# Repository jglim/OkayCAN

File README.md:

# OkayCAN

*The okayest ESP32-S2 CAN development board*

## Features

- Essentially an ESP32-S2 with a CAN transceiver and supporting components.
- Native USB support, saving on an additional USB-UART chip.
- Designed to fit a commonly available OBD enclosure and its 16-pin connectors.
- Each board should cost about US$10 each when assembling about 10 boards, making it fairly affordable in small runs.
- Easy to assemble/manufacture, as all components are on a single side, and most components are surface mounted.
- Uses a USB-C connector, which is easier to interface when the device is installed in difficult-to-reach places.

### Free

This project is permissively licensed (MIT)

- No restrictions and no royalties on private / commercial use.
- The design files (schematic, board) can be downloaded and modified to fit your own requirements.
- Ready-to-use manufacturing files (gerbers, BOM) are also available. Send it to your preferred fab to have the boards made.
- Please feel free to sell the boards that you have made, even if it is a 1:1 clone. There is no need for attribution too.
- The selected [iso-tp stack](https://github.com/lishen2/isotp-c) from [lishen2](https://github.com/lishen2/) that is included in the examples is also MIT-licensed.

---

## Get an OkayCAN

**Build it yourself**

- PCB: [Gerbers are zipped](https://github.com/jglim/OkayCAN/raw/main/Hardware/V1.1/OkayCAN/gerbers/OkayCAN_fab_gerbers_211101.zip) and ready to be uploaded to your fab
- BOM: Almost every component has a matching LCSC part number, and [the CSV](https://github.com/jglim/OkayCAN/blob/main/Hardware/V1.0/OkayCAN/raster/OkayCAN_BOM.csv) works with their BOM upload feature.
    - The only odd part is the OBD2 header (with case), which has to be sourced from marketplaces like Aliexpress
- Assembly: as most of the parts are surface-mounted, getting a stencil will make the process much quicker.

**Buy one**

I'm not assembling any for sale at this time, though I would love to see it being accessible to more people. If you decide to sell complete boards, please let me know so that I may be able to share about it. Everyone is welcome to create and sell clones/variants of the OkayCAN.

---

## Firmware

**[OkayCAN_GettingStarted](https://github.com/jglim/OkayCAN/tree/main/Firmware/Examples/OkayCAN_GettingStarted)**

Get started quickly with this example, which queries a (MB) ECU for parameters such as VIN, part number, and software versions, then displays it on the serial port.

The example will demonstrate communications with an ECU over UDS (a layer above CAN), as well as usage of the serial port over USB CDC. When working properly, the serial should show an output similar to this:

```
Voltage: 11993 mV
00000BBE TX ISO-TP: 22 F1 8C
00000BC3 RX ISO-TP: 62 F1 8C 33 31 33 31 XX XX XX XX
Received Serial Number: 3131XXXX
Voltage: 11979 mV
00000FA7 TX ISO-TP: 22 F1 90
00000FAC RX ISO-TP: 62 F1 90 57 44 44 32 34 36 32 30 30 31 4A XX XX XX XX XX XX
Received VIN Original: WDD2462001JXXXXXX
Voltage: 12003 mV
00001390 TX ISO-TP: 22 F1 A0
00001394 RX ISO-TP: 62 F1 A0 57 44 44 32 34 36 32 30 30 31 4A XX XX XX XX XX XX
Received VIN Current: WDD2462001JXXXXXX
Voltage: 12003 mV
00001779 TX ISO-TP: 22 F1 21
00001783 RX ISO-TP: 62 F1 21 36 35 31 39 30 34 30 33 30 31 36 35 31 39 30 32 33 31 30 31 36 35 31 39 30 33 31 34 33 31
Received Software block data:
6519040301
6519023101
6519031431
Voltage: 11984 mV
00001B62 TX ISO-TP: 22 F1 00
00001B67 RX ISO-TP: 62 F1 00 02 21 31 01
Received Variant ID: 2131
Voltage: 12003 mV
00001F4B TX ISO-TP: 22 F1 11
00001F50 RX ISO-TP: 62 F1 11 36 35 31 39 30 31 30 36 30 31
Received Part Number: 6519010601
...
```

**[OkayCAN_OBD](https://github.com/jglim/OkayCAN/tree/main/Firmware/Examples/OkayCAN_OBD)**

_UNVERIFIED: No vehicle to test on; tested against a simulated ecu on another esp32. Please let me know if this works! --jg_

Queries an OBD-II compliant ECU for its engine speed, vehicle speed, and throttle position. These parameters are typically supported by most ECUs.

A open Wi-Fi network with the name "OkayCAN-OBD" is also created, and serves a simple web page over http at [192.168.4.1](http://192.168.4.1/) . The page shows real-time results of the OBD queries as JSON if they are available.

---

## Hardware

⚠️ Warning: components are rated for 12V only! Please do not connect to 24V systems.

### OkayCAN V1.0

*Please use the newer V1.1 as it addresses a board outline issue*

**Schematic [(PDF)](https://github.com/jglim/OkayCAN/blob/main/Hardware/V1.0/OkayCAN/raster/OkayCAN_Schematic.pdf)**

TL;DR:
**Power**: Vin (USB: 5V, OBD: 12V) with a diode "OR" into a 3.3V buck regulator (MT1470).
**uC**: CAN_TX @ GPIO5, CAN_RX @ GPIO4, VSENSE @ GPIO2 (Divider ratio: Vin-10K,1.6K-GND)
**OBD**: Only CAN TX/RX, VBATT and *chassis* GND are connected. Other pins are NC.

⚠️ The MT1470 regulator only starts operating at 4.5V, which leaves a small margin for the schottky's forward voltage when running off 5V from USB.

ℹ️ The optional 120R CAN resistors should **not** be populated for normal operation as the bus on the vehicle's port normally includes termination resistors.

ℹ️ Test points are available on the back. The ESP32-S2 can also be flashed with an external USB-UART with these test points (like the regular ESP32).

**Board**

ℹ️ V1.0 requires a minor case modification to fit properly, as the OBD connector's sides are too wide. There are two small plastic tabs on the case, near the OBD header which can be safely removed to allow the board to fit properly.

**BOM**

Available [here](https://github.com/jglim/OkayCAN/blob/main/Hardware/V1.0/OkayCAN/raster/OkayCAN_BOM.csv). Budgetary component prices available in [this extended BOM](https://github.com/jglim/OkayCAN/blob/main/Hardware/V1.0/OkayCAN/raster/OkayCAN_Price_Breakdown.csv).

---

### OkayCAN V1.1

*Latest version*

Minor revision to V1.0

- Adjusted board outline to fit the standard cases without modifications
- Added an optional user LED to GPIO16, unpopulated by default
- Minor routing improvements, footprint positions are unchanged and a stencil from V1.0 will still work on this board

---

## DFU

The ESP32-S2 has a USB ROM bootloader which is read-only. This guarantees that a faulty firmware will not brick the device.
OkayCAN includes BOOT and RESET buttons which can be used to bring the device into DFU, to upload a new firmware.

*Enter DFU mode with these steps:*

1. Press BOOT button
2. Press RESET button
3. Release RESET button
4. Release BOOT button

The device can also be put into DFU mode using only the BOOT button. Hold down BOOT while disconnecting and reconnecting the USB cable, then release BOOT.

After flashing the firmware, remember to press RESET once, or reconnect the USB cable to exit DFU and start running your firmware.

---

## Contributing

Please..

- Build cool stuff with the OkayCAN (and let me know if you do, too!).
- Point out and suggest fixes if there are any issues with the hardware design or firmware.
- Add or improve on the existing examples.
- If you fab these boards with a pick-and-place, I would love to hear about your experience.

Need ideas on what to build? Here are some ideas:

- Control an instrument cluster for your racing or truck sim.
- A vehicle communications interface e.g. a J2534 interface.
- Wireless coding/tuning/upgrading via your phone
- Race telemetry/logger with digital gauges

---

## License

MIT

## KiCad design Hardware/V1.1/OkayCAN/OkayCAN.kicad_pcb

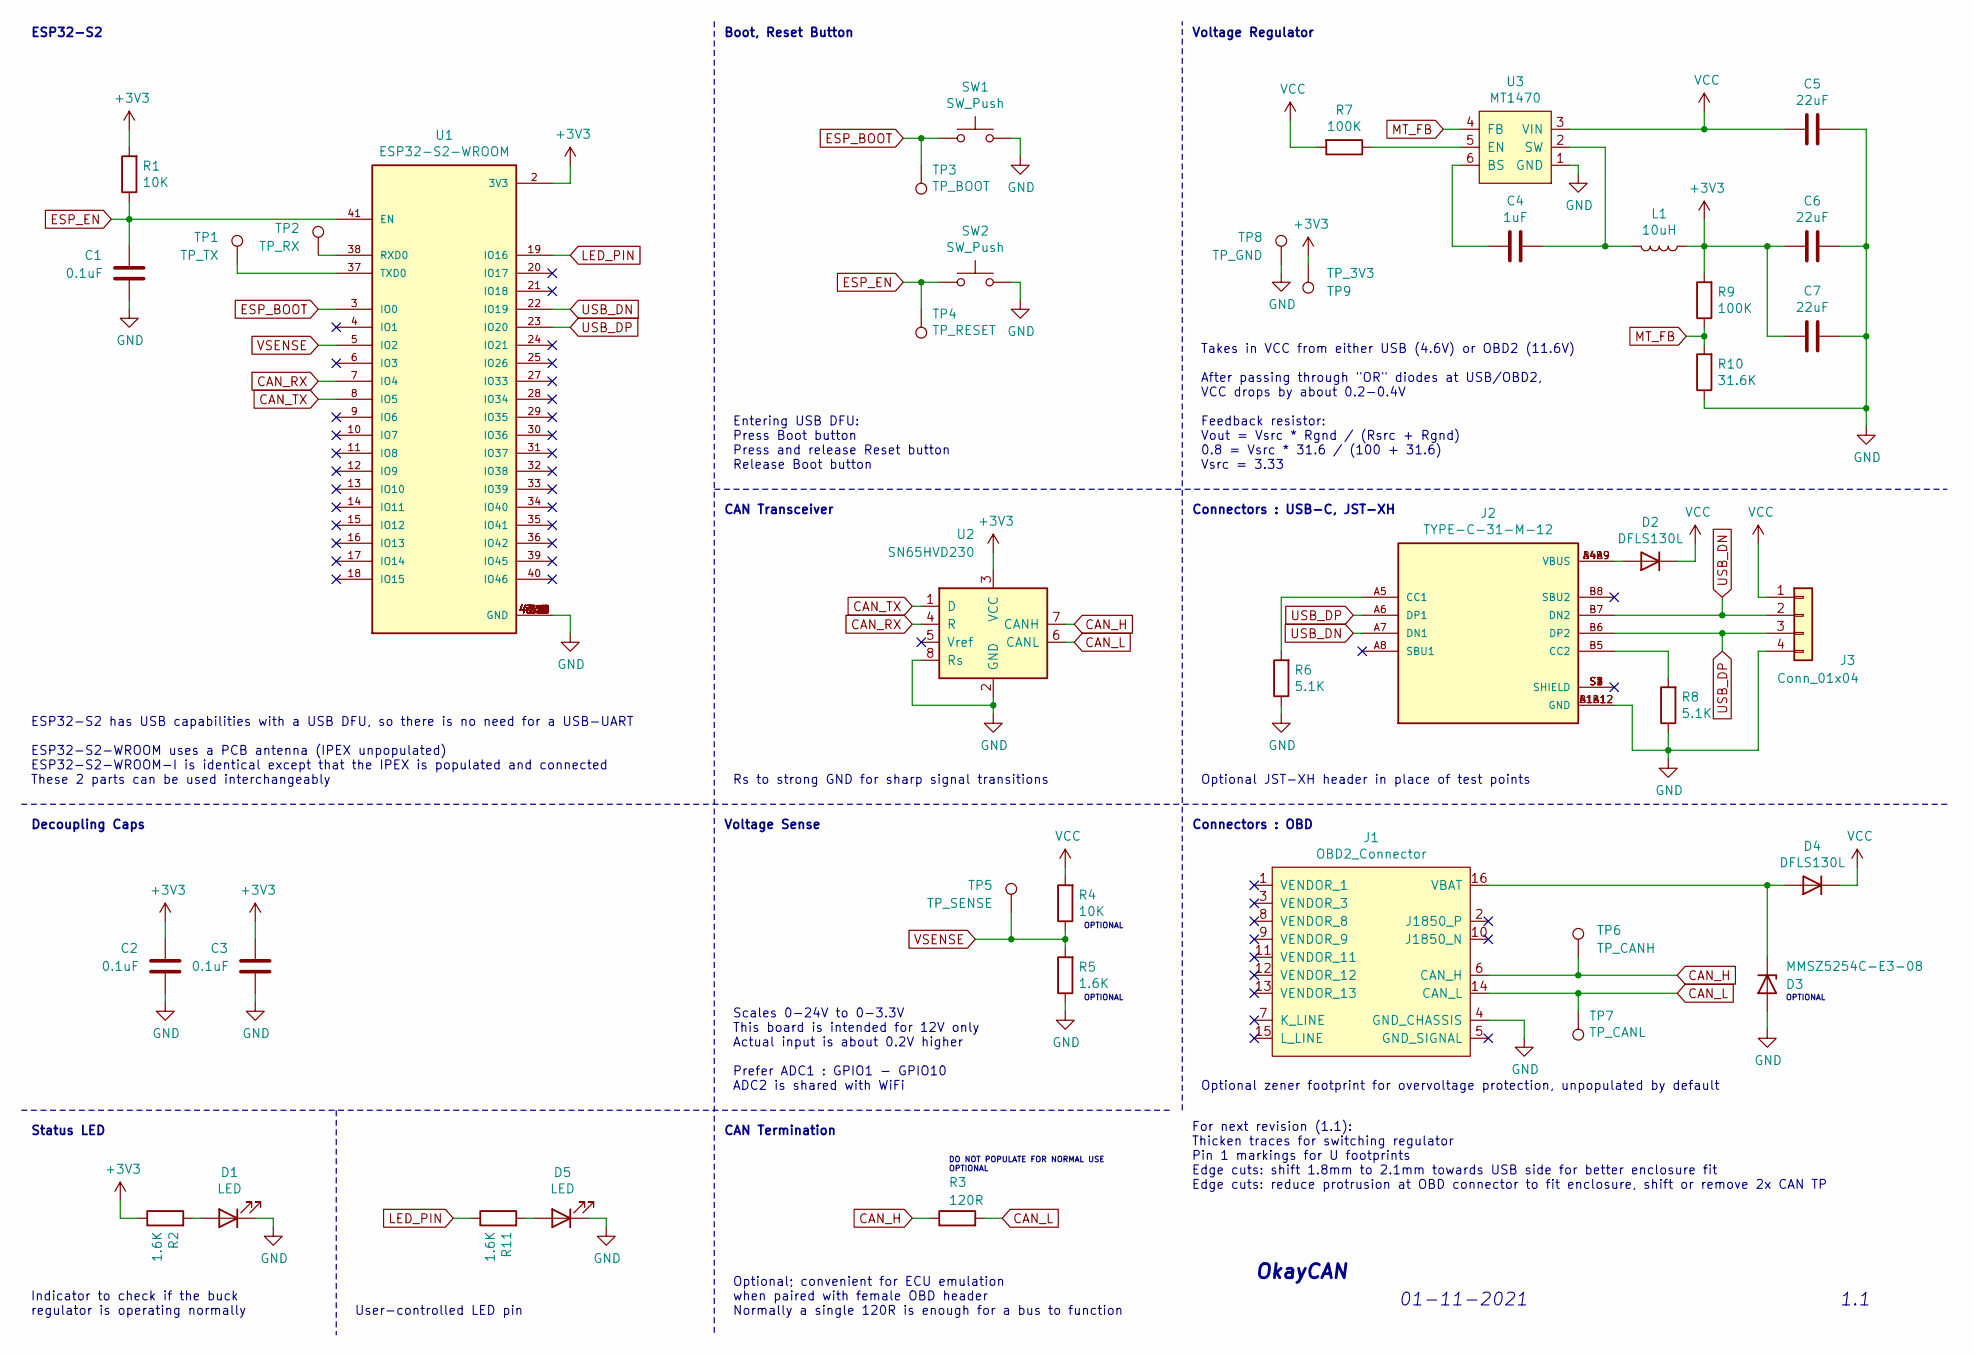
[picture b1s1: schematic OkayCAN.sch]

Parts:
C1, C2, C3: 0.1uF; C_0805_2012Metric_Pad1.15x1.40mm_HandSolder; LCSC C138340
C4: 1uF; C_0805_2012Metric_Pad1.15x1.40mm_HandSolder; LCSC C28323
C5, C6, C7: 22uF; C_0805_2012Metric_Pad1.15x1.40mm_HandSolder; LCSC C45783
D1, D5: LED; LED_0805_2012Metric_Pad1.15x1.40mm_HandSolder; LCSC C84259
D2, D4: DFLS130L; D_PowerDI-123; LCSC C110493
D3: MMSZ5254C-E3-08; D_SOD-123; LCSC C241953
J1: OBD2_Connector; OBD-Male
J2: TYPE-C-31-M-12; HRO_TYPE-C-31-M-12; PARTREV A; LCSC C165948
J3: Conn_01x04; JST_XH_B4B-XH-AM_1x04_P2.50mm_Vertical; LCSC C161871
L1: 10uH; CHILSIN-LVF303012; LCSC C142153
R1, R4: 10K; R_0805_2012Metric_Pad1.15x1.40mm_HandSolder; LCSC C84376
R2, R5, R11: 1.6K; R_0805_2012Metric_Pad1.15x1.40mm_HandSolder; LCSC C17394
R3: 120R; R_1206_3216Metric_Pad1.42x1.75mm_HandSolder; LCSC C175512
R6, R8: 5.1K; R_0805_2012Metric_Pad1.15x1.40mm_HandSolder; LCSC C336831
R7, R9: 100K; R_0805_2012Metric_Pad1.15x1.40mm_HandSolder; LCSC C96346
R10: 31.6K; R_0805_2012Metric_Pad1.15x1.40mm_HandSolder; LCSC C228743
SW1, SW2: SW_Push; HRO-K2-1807; LCSC C502307
TP1: TP_TX; TestPoint_Pad_D1.0mm
TP2: TP_RX; TestPoint_Pad_D1.0mm
TP3: TP_BOOT; TestPoint_Pad_D1.0mm
TP4: TP_RESET; TestPoint_Pad_D1.0mm
TP5: TP_SENSE; TestPoint_Pad_D1.0mm
TP6: TP_CANH; TestPoint_Pad_D1.0mm
TP7: TP_CANL; TestPoint_Pad_D1.0mm
TP8: TP_GND; TestPoint_Pad_D1.0mm
TP9: TP_3V3; TestPoint_Pad_D1.0mm
U1: ESP32-S2-WROOM; XCVR_ESP32-S2-WROOM; PARTREV V1.0; LCSC C967025
U2: SN65HVD230; SOIC-8_3.9x4.9mm_P1.27mm; LCSC C12084
U3: MT1470; SOT-23-6_Handsoldering; LCSC C181781

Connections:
+3V3: C2.1, C3.1, C6.2, C7.2, L1.1, R1.2, R2.1, R9.2, TP9.1, U1.2 (3V3), U2.3 (VCC)
CAN_H: J1.6 (CAN_H), R3.1, TP6.1, U2.7 (CANH)
CAN_L: J1.14 (CAN_L), R3.2, TP7.1, U2.6 (CANL)
CAN_RX: U1.7 (IO4), U2.4 (R)
CAN_TX: U1.8 (IO5), U2.1 (D)
ESP_BOOT: SW1.1, TP3.1, U1.3 (IO0)
ESP_EN: C1.1, R1.1, SW2.1, TP4.1, U1.41 (EN)
GND: C1.2, C2.2, C3.2, C5.1, C6.1, C7.1, D1.1 (K), D3.2 (A), D5.1 (K), J1.4 (GND_CHASSIS), J2.A1B12 (GND), J2.B1A12 (GND), J3.4, R5.1, R6.1, R8.1, R10.1, SW1.2, SW2.2, TP8.1, U1.1 (GND), U1.26 (GND), U1.42 (GND), U1.43.1 (GND), U1.43.2 (GND), U1.43.3 (GND), U1.43.4 (GND), U1.43.5 (GND), U1.43.6 (GND), U1.43.7 (GND), U1.43.8 (GND), U1.43.9 (GND), U1.43.10 (GND), U1.43.11 (GND), U1.43.12 (GND), U1.43.13 (GND), U1.43.14 (GND), U1.43.15 (GND), U1.43.16 (GND), U1.43.17 (GND), U1.43.18 (GND), U1.43.19 (GND), U1.43.20 (GND), U1.43.21 (GND), U2.2 (GND), U2.8 (Rs), U3.1 (GND)
LED_PIN: R11.1, U1.19 (IO16)
MT_FB: R9.1, R10.2, U3.4 (FB)
unnamed: C4.1, L1.2, U3.2 (SW)
unnamed: C4.2, U3.6 (BS)
unnamed: D1.2 (A), R2.2
unnamed: D2.2 (A), J2.A4B9 (VBUS), J2.B4A9 (VBUS)
unnamed: D3.1 (K), D4.2 (A), J1.16 (VBAT)
unnamed: D5.2 (A), R11.2
unnamed: J2.A5 (CC1), R6.2
unnamed: J2.B5 (CC2), R8.2
unnamed: J2.S1 (SHIELD), J2.S2 (SHIELD), J2.S3 (SHIELD), J2.S4 (SHIELD)
unnamed: R7.1, U3.5 (EN)
unnamed: TP1.1, U1.37 (TXD0)
unnamed: TP2.1, U1.38 (RXD0)
USB_DN: J2.A7 (DN1), J2.B7 (DN2), J3.2, U1.22 (IO19)
USB_DP: J2.A6 (DP1), J2.B6 (DP2), J3.3, U1.23 (IO20)
VCC: C5.2, D2.1 (K), D4.1 (K), J3.1, R4.2, R7.2, U3.3 (VIN)
VSENSE: R4.1, R5.2, TP5.1, U1.5 (IO2)

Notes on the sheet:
Takes in VCC from either USB (4.6V) or OBD2 (11.6V) After passing through "OR" diodes at USB/OBD2, VCC drops by about 0.2-0.4V Feedback resistor: Vout = Vsrc * Rgnd / (Rsrc + Rgnd) 0.8 = Vsrc * 31.6 / (100 + 31.6) Vsrc = 3.33
Voltage Regulator
Connectors : USB-C, JST-XH
ESP32-S2
Boot, Reset Button
Voltage Sense
Scales 0-24V to 0-3.3V This board is intended for 12V only Actual input is about 0.2V higher Prefer ADC1 : GPIO1 - GPIO10 ADC2 is shared with WiFi
CAN Transceiver
Optional zener footprint for overvoltage protection, unpopulated by default
Optional JST-XH header in place of test points
Connectors : OBD
Decoupling Caps
Rs to strong GND for sharp signal transitions
Entering USB DFU: Press Boot button Press and release Reset button Release Boot button
CAN Termination
Optional; convenient for ECU emulation when paired with female OBD header Normally a single 120R is enough for a bus to function
OPTIONAL
Status LED
Indicator to check if the buck regulator is operating normally
ESP32-S2 has USB capabilities with a USB DFU, so there is no need for a USB-UART ESP32-S2-WROOM uses a PCB antenna (IPEX unpopulated) ESP32-S2-WROOM-I is identical except that the IPEX is populated and connected These 2 parts can be used interchangeably
For next revision (1.1): Thicken traces for switching regulator Pin 1 markings for U footprints Edge cuts: shift 1.8mm to 2.1mm towards USB side for better enclosure fit Edge cuts: reduce protrusion at OBD connector to fit enclosure, shift or remove 2x CAN TP
DO NOT POPULATE FOR NORMAL USE
OkayCAN
1.1
01-11-2021
User-controlled LED pin

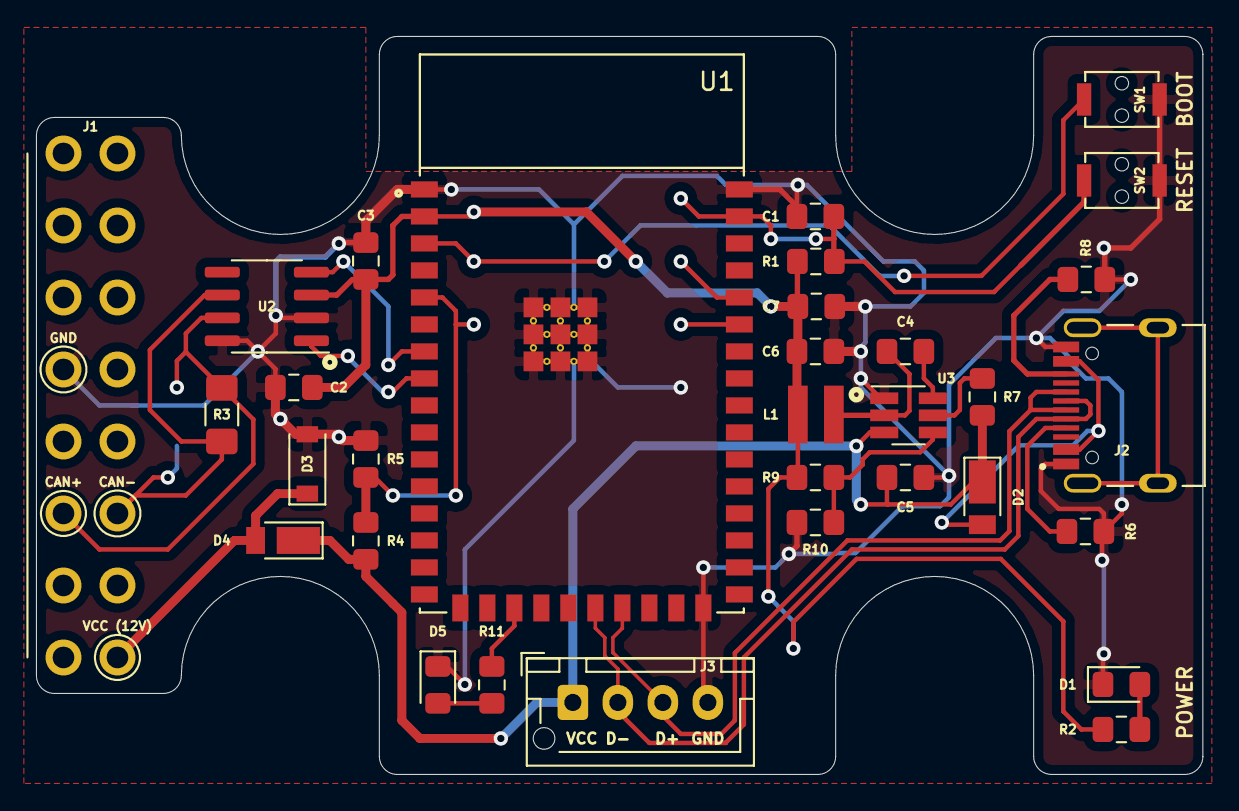
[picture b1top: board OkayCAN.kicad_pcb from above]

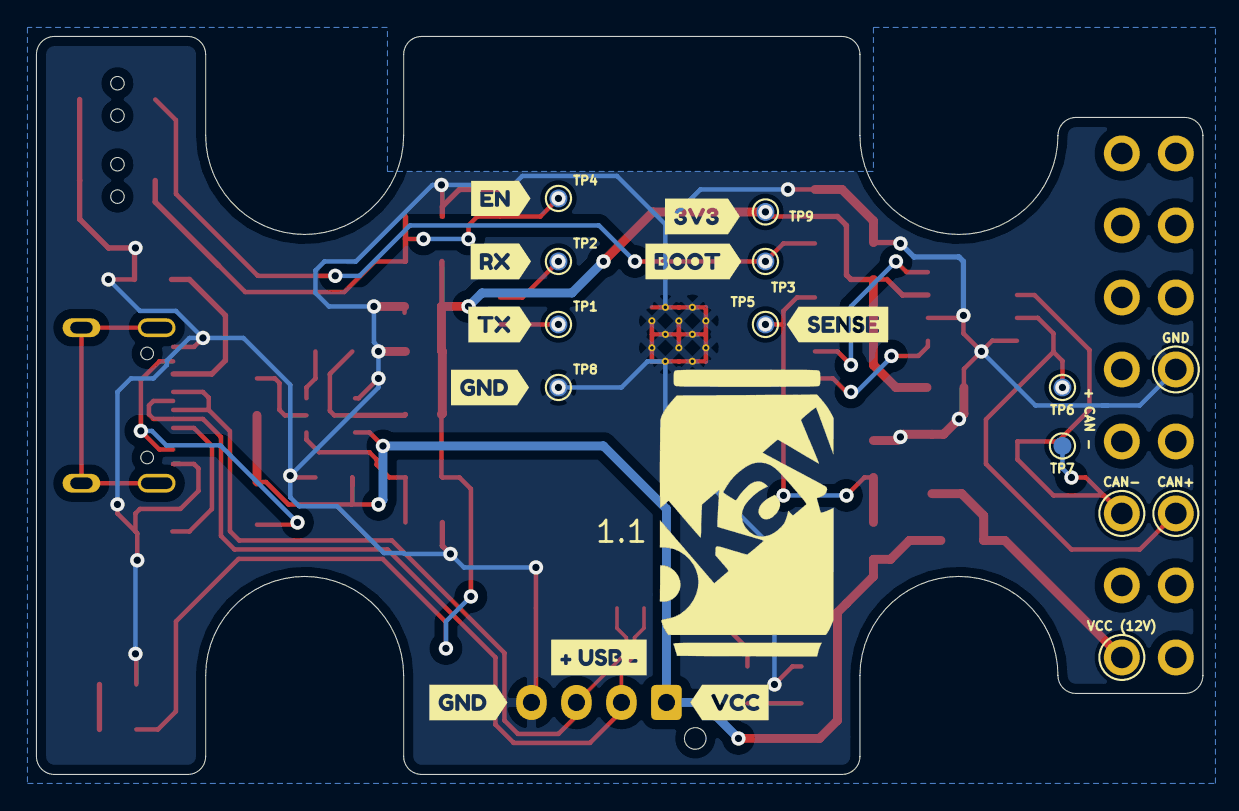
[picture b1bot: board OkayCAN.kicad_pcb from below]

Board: 2 copper layers, 64.8 x 41.0 mm, 51 parts (19 on the bottom side), 26 nets.

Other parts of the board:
kibuzzard-615D3B2E, kibuzzard-615D34A6, kibuzzard-615D34B0, kibuzzard-615D34B9, kibuzzard-615D34C8, kibuzzard-615D34D3, kibuzzard-615D34D3#2, kibuzzard-615D34DF, kibuzzard-615D361C, kibuzzard-615D3669: G***; label

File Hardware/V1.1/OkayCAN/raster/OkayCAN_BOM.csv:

"Id";"Designator";"Package";"Quantity";"Designation";"Supplier and ref";
1;"R11,R5,R2";"R_0805_2012Metric_Pad1.15x1.40mm_HandSolder";3;"1.6K";;;
2;"D5,D1";"LED_0805_2012Metric_Pad1.15x1.40mm_HandSolder";2;"LED";;;
3;"G***";"OkayCAN_Silk";1;"LOGO";;;
4;"kibuzzard-615D3B2E,kibuzzard-615D34D3,kibuzzard-615D3669,kibuzzard-615D361C,kibuzzard-615D34DF,kibuzzard-615D34D3,kibuzzard-615D34C8,kibuzzard-615D34B9,kibuzzard-615D34B0,kibuzzard-615D34A6";"label";10;"G***";;;
5;"TP9";"TestPoint_Pad_D1.0mm";1;"TP_3V3";;;
6;"TP8";"TestPoint_Pad_D1.0mm";1;"TP_GND";;;
7;"TP4";"TestPoint_Pad_D1.0mm";1;"TP_RESET";;;
8;"TP3";"TestPoint_Pad_D1.0mm";1;"TP_BOOT";;;
9;"TP7";"TestPoint_Pad_D1.0mm";1;"TP_CANL";;;
10;"TP6";"TestPoint_Pad_D1.0mm";1;"TP_CANH";;;
11;"TP5";"TestPoint_Pad_D1.0mm";1;"TP_SENSE";;;
12;"TP2";"TestPoint_Pad_D1.0mm";1;"TP_RX";;;
13;"TP1";"TestPoint_Pad_D1.0mm";1;"TP_TX";;;
14;"U3";"SOT-23-6_Handsoldering";1;"MT1470";;;
15;"U2";"SOIC-8_3.9x4.9mm_P1.27mm";1;"SN65HVD230";;;
16;"U1";"XCVR_ESP32-S2-WROOM";1;"ESP32-S2-WROOM";;;
17;"SW2,SW1";"HRO-K2-1807";2;"SW_Push";;;
18;"R10";"R_0805_2012Metric_Pad1.15x1.40mm_HandSolder";1;"31.6K";;;
19;"R9,R7";"R_0805_2012Metric_Pad1.15x1.40mm_HandSolder";2;"100K";;;
20;"R8,R6";"R_0805_2012Metric_Pad1.15x1.40mm_HandSolder";2;"5.1K";;;
21;"R4,R1";"R_0805_2012Metric_Pad1.15x1.40mm_HandSolder";2;"10K";;;
22;"R3";"R_1206_3216Metric_Pad1.42x1.75mm_HandSolder";1;"120R";;;
23;"L1";"CHILSIN-LVF303012";1;"10uH";;;
24;"J3";"JST_XH_B4B-XH-AM_1x04_P2.50mm_Vertical";1;"Conn_01x04";;;
25;"J2";"HRO_TYPE-C-31-M-12";1;"TYPE-C-31-M-12";;;
26;"J1";"OBD-Male";1;"OBD2_Connector";;;
27;"D4,D2";"D_PowerDI-123";2;"DFLS130L";;;
28;"D3";"D_SOD-123";1;"MMSZ5254C-E3-08";;;
29;"C7,C6,C5";"C_0805_2012Metric_Pad1.15x1.40mm_HandSolder";3;"22uF";;;
30;"C4";"C_0805_2012Metric_Pad1.15x1.40mm_HandSolder";1;"1uF";;;
31;"C3,C2,C1";"C_0805_2012Metric_Pad1.15x1.40mm_HandSolder";3;"0.1uF";;;

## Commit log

2021-11-01 Initial commit
    Snapshot of V1 board (fabbed)
2021-11-03 Add price breakdown
    For approximating cost per device
2021-11-03 Add firmware example for GettingStarted
2021-11-03 Update example (GettingStarted) to not use a broadcast tx address
2021-11-03 Add example's readme
2021-11-06 Add readme contents
2021-11-07 Add example for OBD over HTTP
2021-11-07 Add obd example to readme
2021-11-07 Add V1.1
